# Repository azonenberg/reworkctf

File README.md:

# reworkctf

## What is it?

This is a points-based challenge board intended for practicing of PCB rework and circuit editing skills. This is not a circuit *debug* challenge. The defect for each stage is well documented, your task is to correct it so that the circuit functions properly.

This is also not a learn-to-solder kit. If you're not comfortable populating boards with 0402 passives and larger pitch (0.8mm) BGAs, this is probably not a project you want to undertake until you have the basics down first.

That said, the challenges range from very easy to fairly difficult, so it's totally fine to try some of them then put the board on a shelf for a while until your skills improve. Inner layer circuit edits are among the most challenging rework tasks around, there's a reason they're worth the most points!

This is also intended to be a relatively low-cost board so you can practice without the pressure of reworking a production design with a big FPGA and five-digit price tag. If you destroy a couple of these boards then get the hang of things and your third attempt succeeds, great - you've learned something.

And if the board survives, you've got a STM32H750 dev platform with a UART, two PMODs, a SPI flash, and a lot of LEDs to maybe do something useful with.

IMPORTANT NOTE: Read the challenge list before populating the front side of the PCB. Some of the BGA-site challenges have two versions, an "easy" version which can be done on a bare PCB before populating allowing easy access to the BGA footprint, and a "hard" version which requires you populate the board before doing the rework. Unless you want to do the hard version twice, don't populate the board until you've done the easier ones. This does require doing some of the challenges out of order, unless you want to make two boards and do different challenges on each.

Most notably, the following challenges should be done before populating the BGA:
* Challenge 13

## How do I complete a given challenge?

It's up to you, within reason. If you are able to restore the intended electrical connectivity to the point that the firmware lights up the corresponding "complete" LED and you've followed any restrictions listed in the problem text, you've done it. Please follow the spirit of the challenges, many of them can be "cheated" by jumpering adjacent pins on the MCU together or similar but the point of this board is skill development. If you don't actually fix the intended defect you're not learning.

Almost all challenges are electrically testable by the MCU firmware; those that involve soldermask or silkscreen rework can be graded by visual inspection of the board. If those look good, they probably are.

The [IPC rework guides](https://www.circuitrework.com/guides/guides.html) are a good starting point for general repair techniques.

If you get really stuck on a specific challenge you can message me on Mastodon at[@azonenberg@ioc.exchange](https://ioc.exchange/@azonenberg]) but please make a reasonable attempt to plan a solution first.

## I still have an old rev board, where's the info for that?

The legacy revision 1 challenge, built around a Spartan-3A FPGA, can be found in the "v1" directory and is being kept there in case anybody has an old board and wants to refer to the design. Anyone building the challenge now should use the v2 design which is based on parts that (as of this writing in early 2026) are readily available and inexpensive.

## What tools are required?

A fine point soldering iron, good tweezers, and hot air rework station are a must to attempt any of the challenges. A stereo microscope is strongly recommended.

The silkscreen and solder mask repair challenges require UV or heat cured coating materials and a curing lamp or oven appropriate for the coating chemistry. UV resin allows much more rapid iteration and avoids heat stress on the remainder of the system so we strongly recommend it over heat cure systems.

Surface trace cuts and rerouting require a scalpel or rotary tool/mill with very fine cutters. While the inner layer circuit edits are *possible* to complete with hand scraping or a handheld rotary tool, we strongly recommend use of a 3-axis mill and microscope for the highest grade results and greatest chance of success.

## What are the challenges?

See [the list here](/CHALLENGES.md). Each challenge is marked with silkscreened text on the PCB to make it easy to find.

## What is the "Free Play Area"?

A big pile of component footprints and traces not connected to anything else. Invent your own challenges or use it to practice for the official ones.

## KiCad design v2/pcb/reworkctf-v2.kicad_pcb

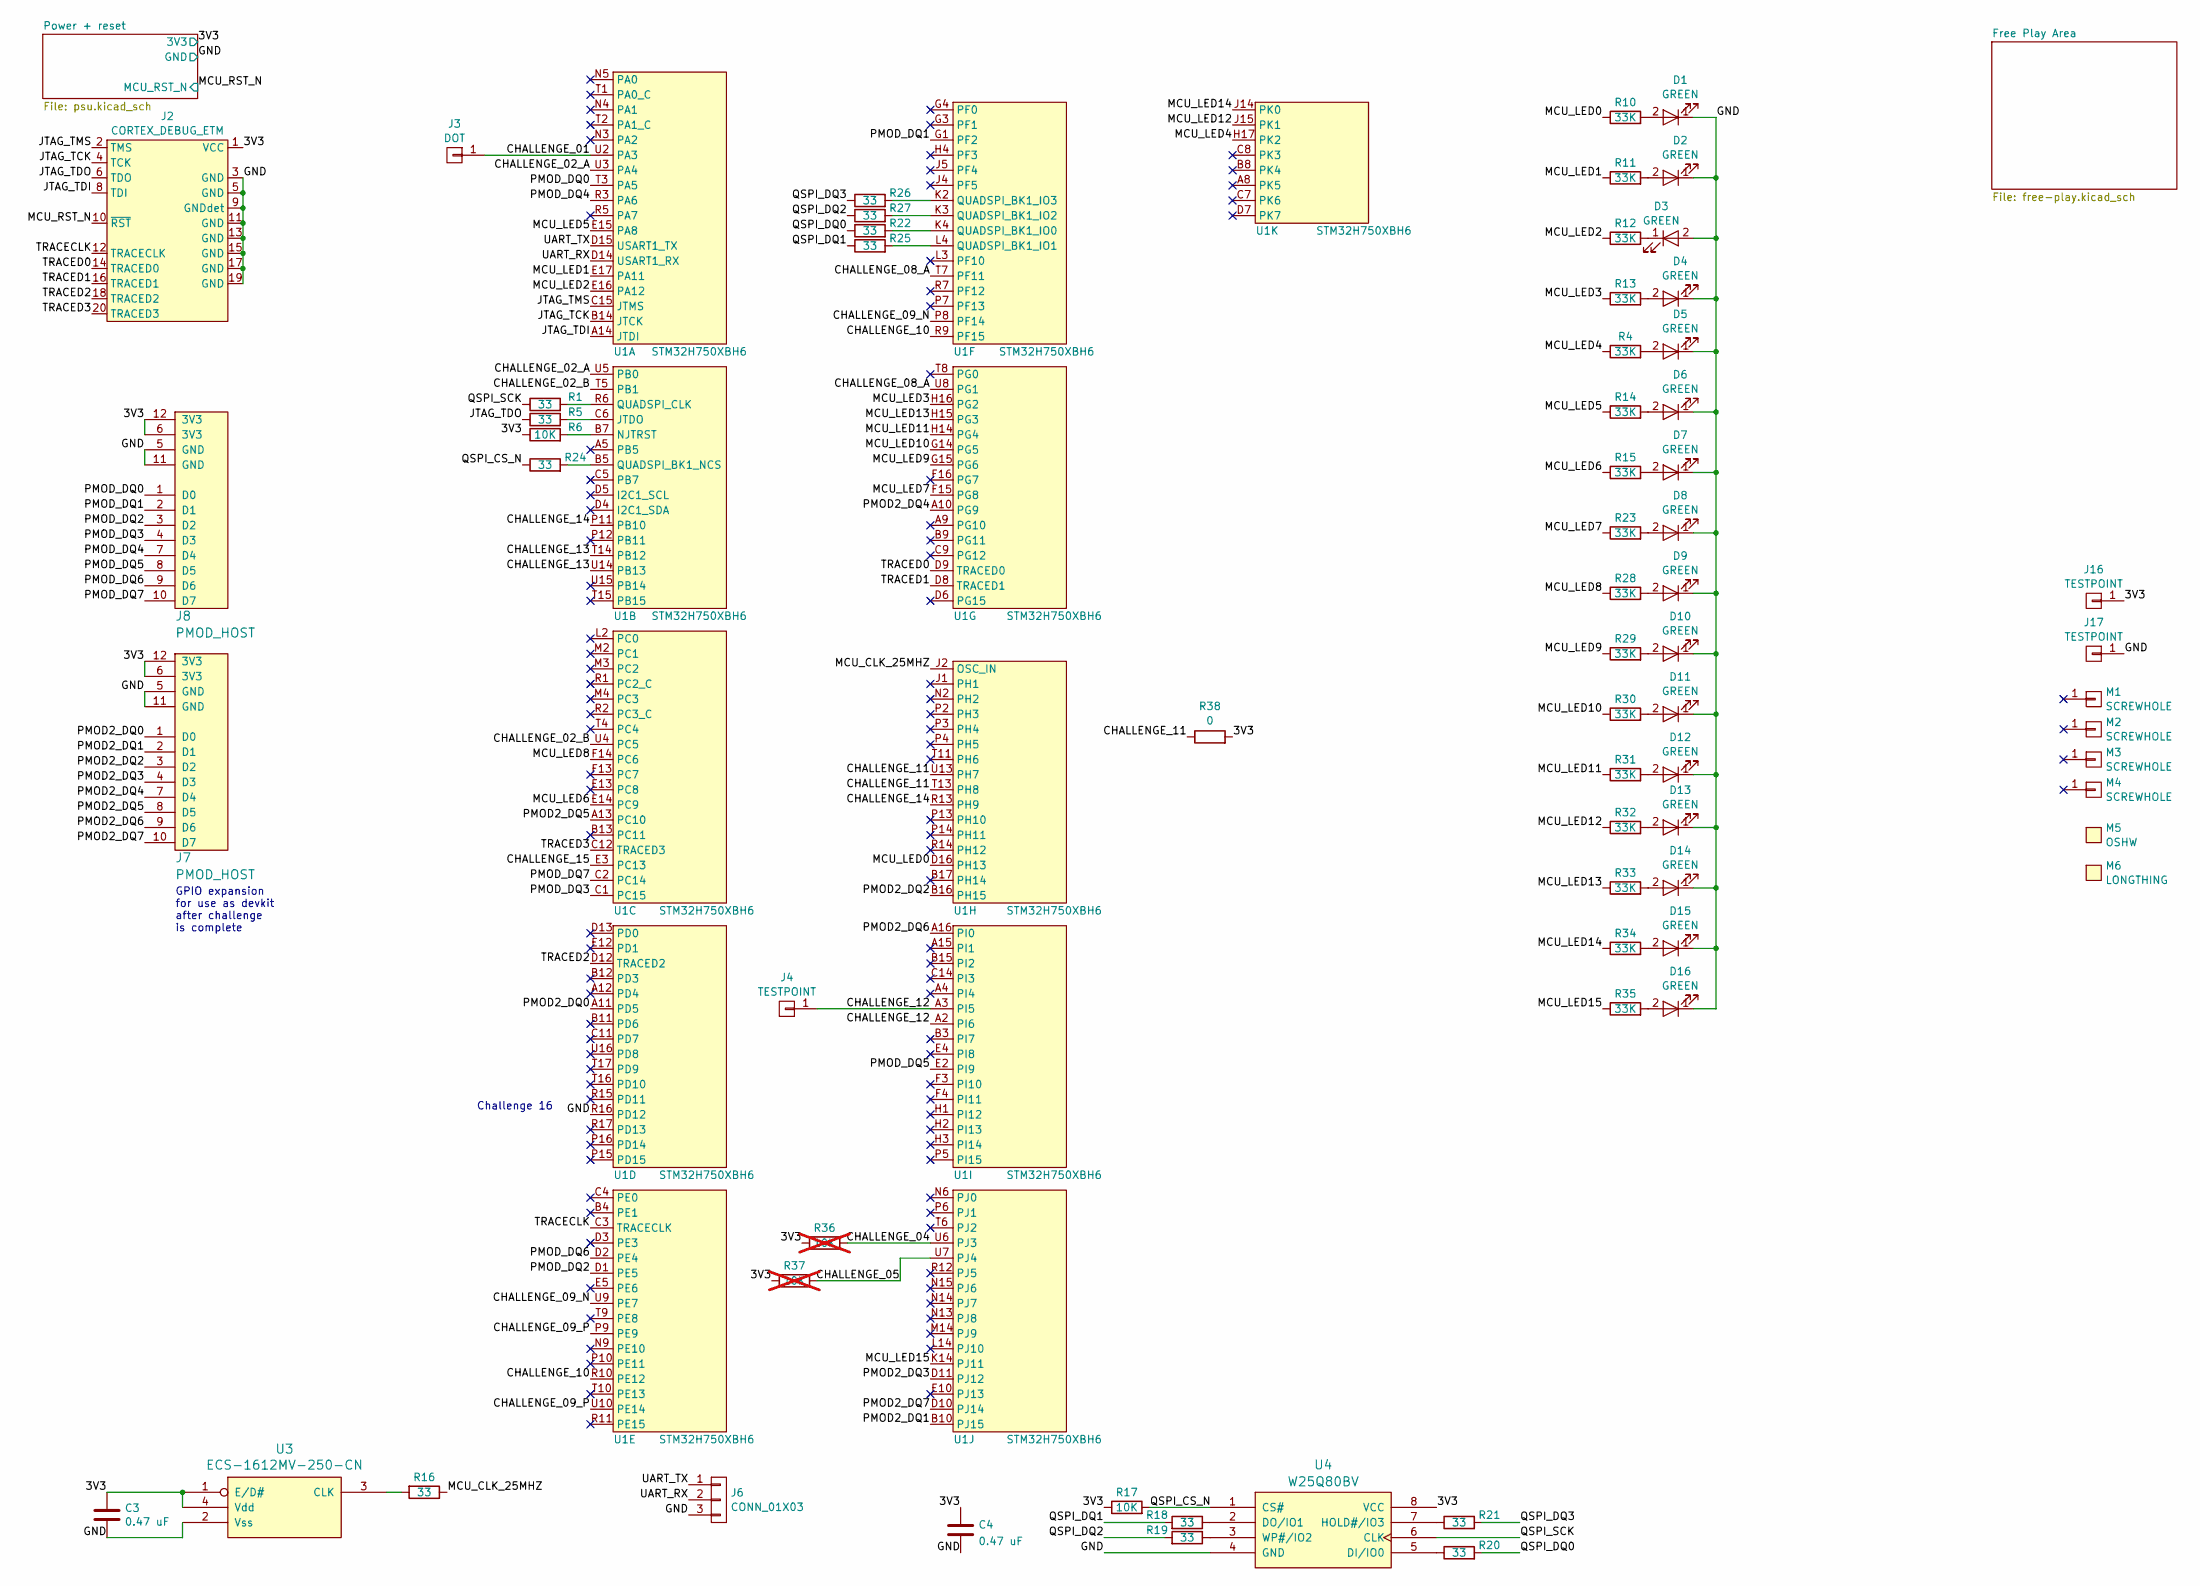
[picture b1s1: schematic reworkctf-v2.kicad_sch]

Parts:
C3, C4: 0.47 uF; EIA_0402_CAP_NOSILK
D1, D2, D3, D4, D5, D6, D7, D8, D9, D10, D11, D12, D13, D14, D15, D16: GREEN; EIA_0402_LED
J2: CORTEX_DEBUG_ETM; CONN_HEADER_1.27MM_2x10_SMT_SAMTEC_FTSH-110-01-L-DV-K
J3: DOT; TESTPOINT_SMT_0.5MM
J4, J16, J17: TESTPOINT; TESTPOINT_SMT_0.5MM
J6: CONN_01X03; CONN_HEADER_2.54MM_1x3_REFLOW
J7, J8: PMOD_HOST; CONN_HEADER_2.54MM_2x6_RA_PMOD_HOST
M1, M2, M3, M4: SCREWHOLE; MECHANICAL_CLEARANCEHOLE_4_40
M5: OSHW; Logo_silk_OSHW_6x6mm
M6: LONGTHING; LONGTHING-1200DPI
R1, R5, R16, R18, R19, R20, R21, R22, R24, R25, R26, R27: 33; EIA_0402_RES_NOSILK
R4, R10, R11, R12, R13, R14, R15, R23, R28, R29, R30, R31, R32, R33, R34, R35: 33K; EIA_0402_RES_NOSILK
R6, R17: 10K; EIA_0402_RES_NOSILK
R36: 10K; EIA_0201_RES_NOSILK; not fitted
R37: 10K; EIA_01005_RES_NOSILK; not fitted
R38: 0; EIA_0402_RES_NOSILK
U1: STM32H750XBH6; BGA_265_14x14_DEPOP_0.8MM
U3: ECS-1612MV-250-CN; OSCILLATOR_1.6x1.2
U4: W25Q80BV; SOIC_8_5.3MM

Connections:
/3V3: C3.1, C4.1, J2.1 (VCC), J7.6 (3V3), J7.12 (3V3), J8.6 (3V3), J8.12 (3V3), J16.1, R6.1, R17.1, R36.1, R37.1, R38.2, U3.1 (E/D#), U3.4 (Vdd), U4.8 (VCC); also elsewhere on the board
/CHALLENGE_01: J3.1, U1.U2 (PA3)
/CHALLENGE_02_A: U1.U3 (PA4), U1.U5 (PB0)
/CHALLENGE_02_B: U1.T5 (PB1), U1.U4 (PC5)
/CHALLENGE_04: R36.2, U1.U6 (PJ3)
/CHALLENGE_05: R37.2, U1.U7 (PJ4)
/CHALLENGE_08_A: U1.T7 (PF11), U1.U8 (PG1)
/CHALLENGE_09_N: U1.P8 (PF14), U1.U9 (PE7)
/CHALLENGE_09_P: U1.P9 (PE9), U1.U10 (PE14)
/CHALLENGE_10: U1.R9 (PF15), U1.R10 (PE12)
/CHALLENGE_11: R38.1, U1.T13 (PH8), U1.U13 (PH7)
/CHALLENGE_12: J4.1, U1.A2 (PI6), U1.A3 (PI5)
/CHALLENGE_13: U1.T14 (PB12), U1.U14 (PB13)
/CHALLENGE_14: U1.P11 (PB10), U1.R13 (PH9)
/CHALLENGE_15: U1.E3 (PC13)
/GND: C3.2, C4.2, D1.1 (K), D2.1 (K), D3.2 (A), D4.1 (K), D5.1 (K), D6.1 (K), D7.1 (K), D8.1 (K), D9.1 (K), D10.1 (K), D11.1 (K), D12.1 (K), D13.1 (K), D14.1 (K), D15.1 (K), D16.1 (K), J2.3 (GND), J2.5 (GND), J2.9 (GNDdet), J2.11 (GND), J2.13 (GND), J2.15 (GND), J2.17 (GND), J2.19 (GND), J6.3, J7.5 (GND), J7.11 (GND), J8.5 (GND), J8.11 (GND), J17.1, U1.R16 (PD12), U3.2 (Vss), U4.4 (GND); also elsewhere on the board
/JTAG_TCK: J2.4 (TCK), U1.B14 (JTCK)
/JTAG_TDI: J2.8 (TDI), U1.A14 (JTDI)
/JTAG_TDO: J2.6 (TDO), R5.1
/JTAG_TMS: J2.2 (TMS), U1.C15 (JTMS)
/MCU_CLK_25MHZ: R16.1, U1.J2 (OSC_IN)
/MCU_LED0: R10.1, U1.D16 (PH13)
/MCU_LED1: R11.1, U1.E17 (PA11)
/MCU_LED2: R12.1, U1.E16 (PA12)
/MCU_LED3: R13.1, U1.H16 (PG2)
/MCU_LED4: R4.1, U1.H17 (PK2)
/MCU_LED5: R14.1, U1.E15 (PA8)
/MCU_LED6: R15.1, U1.E14 (PC9)
/MCU_LED7: R23.1, U1.F15 (PG8)
/MCU_LED8: R28.1, U1.F14 (PC6)
/MCU_LED9: R29.1, U1.G15 (PG6)
/MCU_LED10: R30.1, U1.G14 (PG5)
/MCU_LED11: R31.1, U1.H14 (PG4)
/MCU_LED12: R32.1, U1.J15 (PK1)
/MCU_LED13: R33.1, U1.H15 (PG3)
/MCU_LED14: R34.1, U1.J14 (PK0)
/MCU_LED15: R35.1, U1.K14 (PJ11)
/MCU_RST_N: J2.10 (~RST); also elsewhere on the board
/PMOD2_DQ0: J7.1 (D0), U1.A11 (PD5)
/PMOD2_DQ1: J7.2 (D1), U1.B10 (PJ15)
/PMOD2_DQ2: J7.3 (D2), U1.B16 (PH15)
/PMOD2_DQ3: J7.4 (D3), U1.D11 (PJ12)
/PMOD2_DQ4: J7.7 (D4), U1.A10 (PG9)
/PMOD2_DQ5: J7.8 (D5), U1.A13 (PC10)
/PMOD2_DQ6: J7.9 (D6), U1.A16 (PI0)
/PMOD2_DQ7: J7.10 (D7), U1.D10 (PJ14)
/PMOD_DQ0: J8.1 (D0), U1.T3 (PA5)
/PMOD_DQ1: J8.2 (D1), U1.G1 (PF2)
/PMOD_DQ2: J8.3 (D2), U1.D1 (PE5)
/PMOD_DQ3: J8.4 (D3), U1.C1 (PC15)
/PMOD_DQ4: J8.7 (D4), U1.R3 (PA6)
/PMOD_DQ5: J8.8 (D5), U1.E2 (PI9)
/PMOD_DQ6: J8.9 (D6), U1.D2 (PE4)
/PMOD_DQ7: J8.10 (D7), U1.C2 (PC14)
/QSPI_CS_N: R17.2, R24.1, U4.1 (CS#)
/QSPI_DQ0: R20.2, R22.1
/QSPI_DQ1: R18.2, R25.1
/QSPI_DQ2: R19.2, R27.1
/QSPI_DQ3: R21.2, R26.1
/QSPI_SCK: R1.1, U4.6 (CLK)
/TRACECLK: J2.12 (TRACECLK), U1.C3 (TRACECLK)
/TRACED0: J2.14 (TRACED0), U1.D9 (TRACED0)
/TRACED1: J2.16 (TRACED1), U1.D8 (TRACED1)
/TRACED2: J2.18 (TRACED2), U1.D12 (TRACED2)
/TRACED3: J2.20 (TRACED3), U1.C12 (TRACED3)
/UART_RX: J6.2, U1.D14 (USART1_RX)
/UART_TX: J6.1, U1.D15 (USART1_TX)
unnamed: D1.2 (A), R10.2
unnamed: D2.2 (A), R11.2
unnamed: D3.1 (K), R12.2
unnamed: D4.2 (A), R13.2
unnamed: D5.2 (A), R4.2
unnamed: D6.2 (A), R14.2
unnamed: D7.2 (A), R15.2
unnamed: D8.2 (A), R23.2
unnamed: D9.2 (A), R28.2
unnamed: D10.2 (A), R29.2
unnamed: D11.2 (A), R30.2
unnamed: D12.2 (A), R31.2
unnamed: D13.2 (A), R32.2
unnamed: D14.2 (A), R33.2
unnamed: D15.2 (A), R34.2
unnamed: D16.2 (A), R35.2
unnamed: R1.2, U1.R6 (QUADSPI_CLK)
unnamed: R5.2, U1.C6 (JTDO)
unnamed: R6.2, U1.B7 (NJTRST)
unnamed: R24.2, U1.B5 (QUADSPI_BK1_NCS)
unnamed: R26.2, U1.K2 (QUADSPI_BK1_IO3)
unnamed: R27.2, U1.K3 (QUADSPI_BK1_IO2)
unnamed: R22.2, U1.K4 (QUADSPI_BK1_IO0)
unnamed: R25.2, U1.L4 (QUADSPI_BK1_IO1)
unnamed: R16.2, U3.3 (CLK)
unnamed: R20.1, U4.5 (DI/IO0)
unnamed: R18.1, U4.2 (DO/IO1)
unnamed: R21.1, U4.7 (HOLD#/IO3)
unnamed: R19.1, U4.3 (WP#/IO2)

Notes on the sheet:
Challenge 16
GPIO expansion for use as devkit after challenge is complete

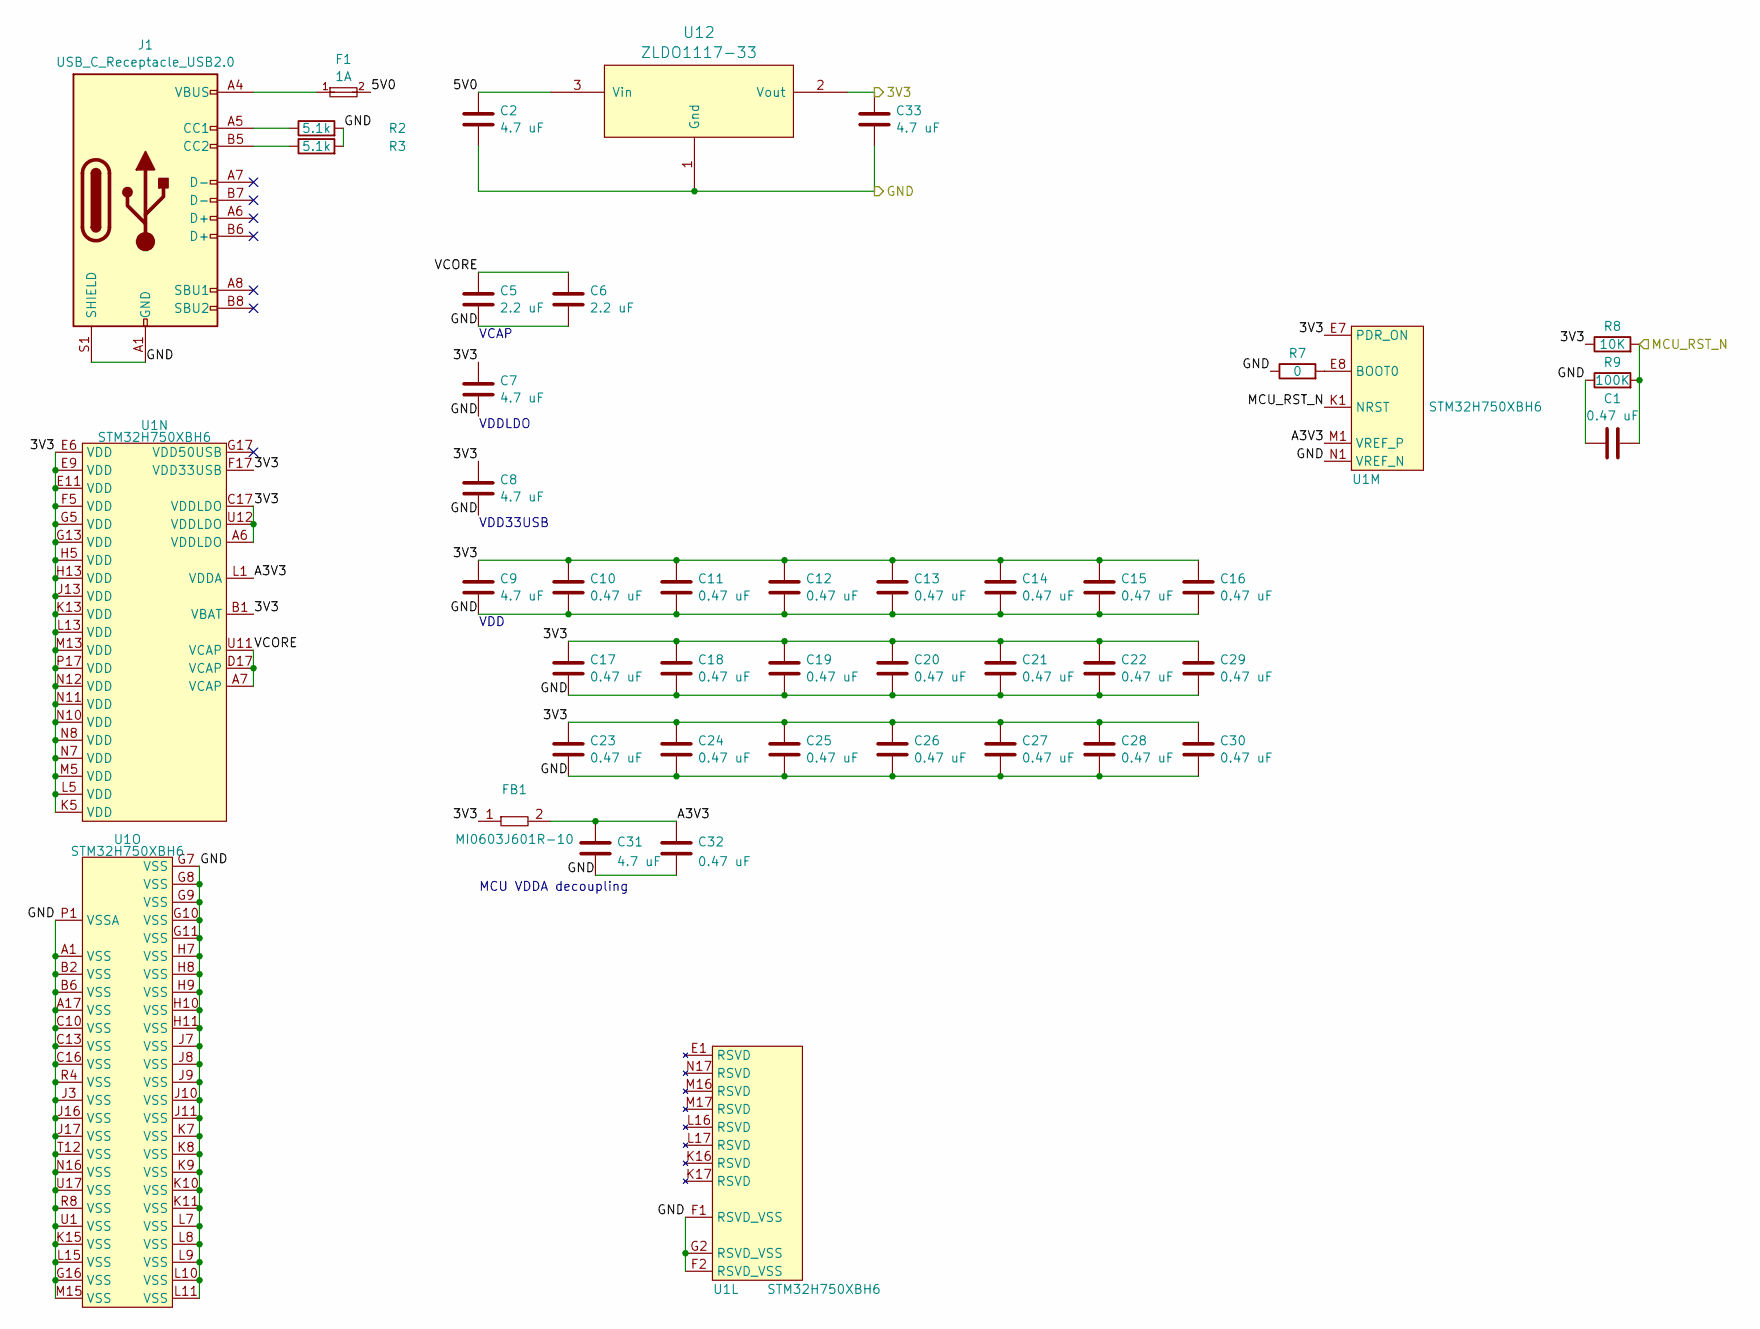
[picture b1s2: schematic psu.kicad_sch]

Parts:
C1, C10, C11, C12, C13, C14, C15, C16, C17, C18, C19, C20, C21, C22, C23, C24, C25, C26, C27, C28, C29, C30, C32: 0.47 uF; EIA_0402_CAP_NOSILK
C2, C7, C8, C9, C31, C33: 4.7 uF; EIA_0603_CAP_NOSILK
C5, C6: 2.2 uF; EIA_0603_CAP_NOSILK
F1: 1A; EIA_0402_RES_NOSILK
FB1: MI0603J601R-10; EIA_0603_INDUCTOR_NOSILK
J1: USB_C_Receptacle_USB2.0; GCT_USB4500-03-0-A
R2, R3: 5.1k; EIA_0402_RES_NOSILK
R7: 0; EIA_0402_RES_NOSILK
R8: 10K; EIA_0402_RES_NOSILK
R9: 100K; EIA_0402_RES_NOSILK
U1: STM32H750XBH6; BGA_265_14x14_DEPOP_0.8MM
U12: ZLDO1117-33; SOT223-4

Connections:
/3V3: C7.1, C8.1, C9.1, C10.1, C11.1, C12.1, C13.1, C14.1, C15.1, C16.1, C17.1, C18.1, C19.1, C20.1, C21.1, C22.1, C23.1, C24.1, C25.1, C26.1, C27.1, C28.1, C29.1, C30.1, C33.1, FB1.1, R8.1, U1.A6 (VDDLDO), U1.B1 (VBAT), U1.C17 (VDDLDO), U1.E6 (VDD), U1.E7 (PDR_ON), U1.E9 (VDD), U1.E11 (VDD), U1.F5 (VDD), U1.F17 (VDD33USB), U1.G5 (VDD), U1.G13 (VDD), U1.H5 (VDD), U1.H13 (VDD), U1.J13 (VDD), U1.K5 (VDD), U1.K13 (VDD), U1.L5 (VDD), U1.L13 (VDD), U1.M5 (VDD), U1.M13 (VDD), U1.N7 (VDD), U1.N8 (VDD), U1.N10 (VDD), U1.N11 (VDD), U1.N12 (VDD), U1.P17 (VDD), U1.U12 (VDDLDO), U12.2 (Vout); also elsewhere on the board
/GND: C1.1, C2.2, C5.2, C6.2, C7.2, C8.2, C9.2, C10.2, C11.2, C12.2, C13.2, C14.2, C15.2, C16.2, C17.2, C18.2, C19.2, C20.2, C21.2, C22.2, C23.2, C24.2, C25.2, C26.2, C27.2, C28.2, C29.2, C30.2, C31.2, C32.2, C33.2, J1.A1 (GND), J1.A12 (GND), J1.B1 (GND), J1.B12 (GND), J1.S1 (SHIELD), R2.2, R3.2, R7.1, R9.1, U1.A1 (VSS), U1.A17 (VSS), U1.B2 (VSS), U1.B6 (VSS), U1.C10 (VSS), U1.C13 (VSS), U1.C16 (VSS), U1.F1 (RSVD_VSS), U1.F2 (RSVD_VSS), U1.G2 (RSVD_VSS), U1.G7 (VSS), U1.G8 (VSS), U1.G9 (VSS), U1.G10 (VSS), U1.G11 (VSS), U1.G16 (VSS), U1.H7 (VSS), U1.H8 (VSS), U1.H9 (VSS), U1.H10 (VSS), U1.H11 (VSS), U1.J3 (VSS), U1.J7 (VSS), U1.J8 (VSS), U1.J9 (VSS), U1.J10 (VSS), U1.J11 (VSS), U1.J16 (VSS), U1.J17 (VSS), U1.K7 (VSS), U1.K8 (VSS), U1.K9 (VSS), U1.K10 (VSS), U1.K11 (VSS), U1.K15 (VSS), U1.L7 (VSS), U1.L8 (VSS), U1.L9 (VSS), U1.L10 (VSS), U1.L11 (VSS), U1.L15 (VSS), U1.M15 (VSS), U1.N1 (VREF_N), U1.N16 (VSS), U1.P1 (VSSA), U1.R4 (VSS), U1.R8 (VSS), U1.T12 (VSS), U1.U1 (VSS), U1.U17 (VSS), U12.1 (Gnd); also elsewhere on the board
/MCU_RST_N: C1.2, R8.2, R9.2, U1.K1 (NRST); also elsewhere on the board
/Power + reset/5V0: C2.1, F1.2, U12.3 (Vin)
/Power + reset/A3V3: C31.1, C32.1, FB1.2, U1.L1 (VDDA), U1.M1 (VREF_P)
/Power + reset/VCORE: C5.1, C6.1, U1.A7 (VCAP), U1.D17 (VCAP), U1.U11 (VCAP)
unnamed: F1.1, J1.A4 (VBUS), J1.A9 (VBUS), J1.B4 (VBUS), J1.B9 (VBUS)
unnamed: J1.A5 (CC1), R2.1
unnamed: J1.B5 (CC2), R3.1
unnamed: R7.2, U1.E8 (BOOT0)

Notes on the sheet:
VDD
MCU VDDA decoupling
VDDLDO
VCAP
VDD33USB

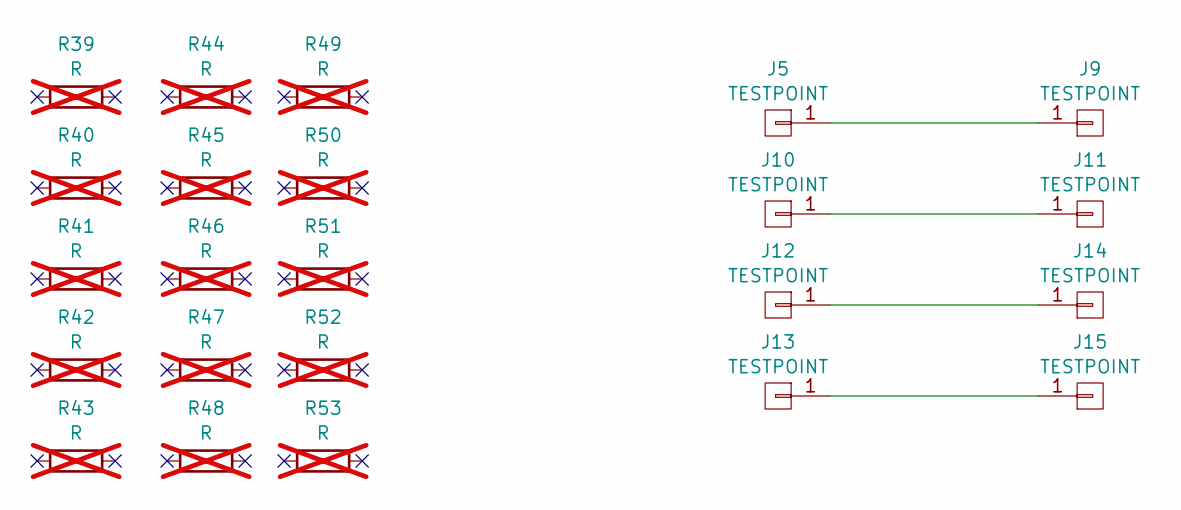
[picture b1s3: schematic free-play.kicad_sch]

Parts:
J5, J9, J10, J11, J12, J13, J14, J15: TESTPOINT; TESTPOINT_SMT_0.5MM
R39, R40, R41, R42, R43, R44, R45, R46, R47, R48, R49, R50, R51, R52, R53: R; EIA_0402_RES_NOSILK; not fitted

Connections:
unnamed: J5.1, J9.1
unnamed: J10.1, J11.1
unnamed: J12.1, J14.1
unnamed: J13.1, J15.1

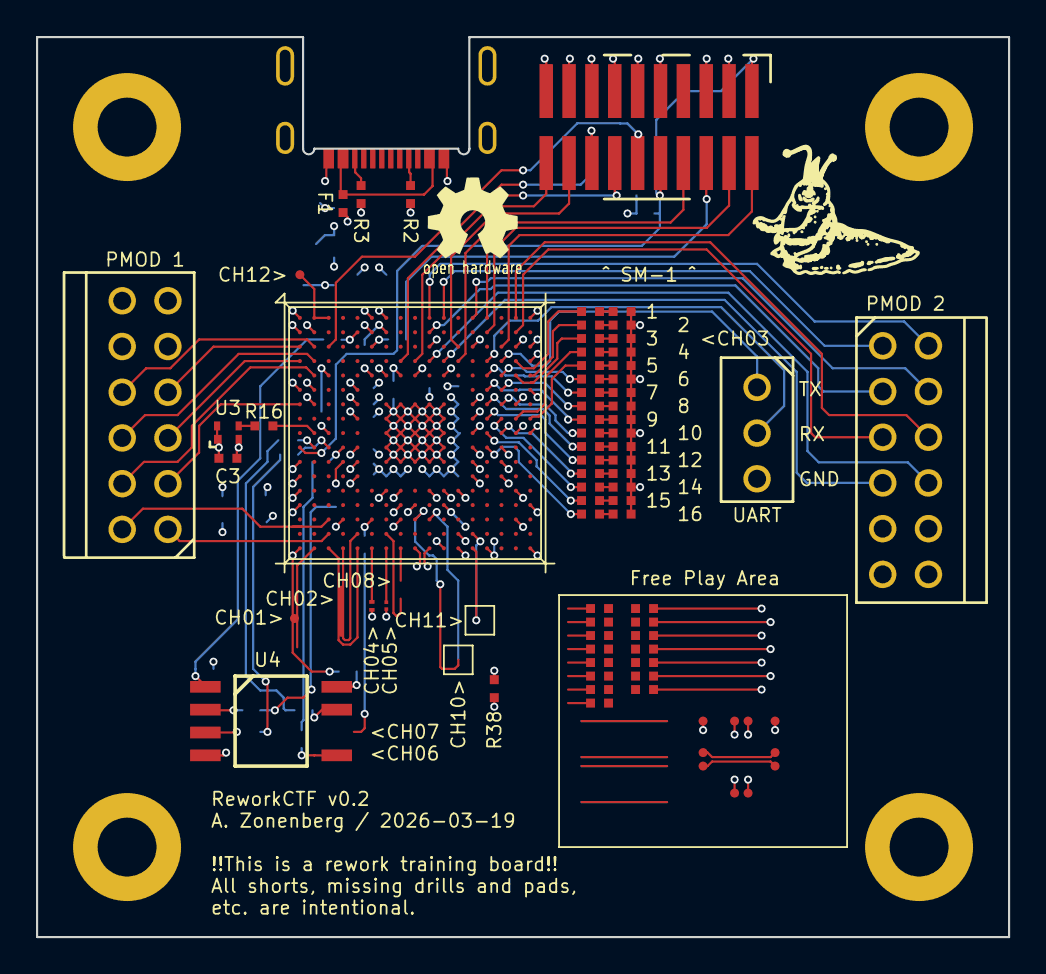
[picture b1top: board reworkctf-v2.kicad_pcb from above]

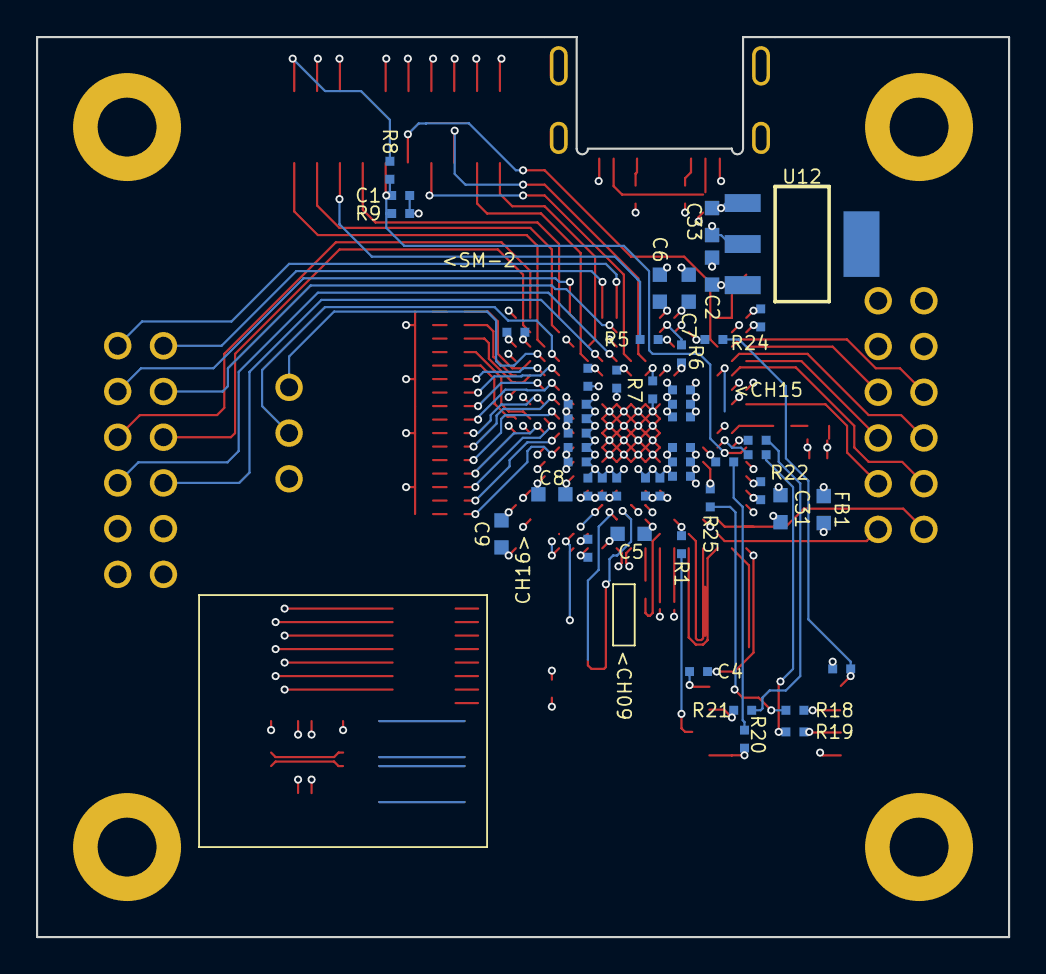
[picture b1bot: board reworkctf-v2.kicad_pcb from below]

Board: 4 copper layers, 54.0 x 50.0 mm, 131 parts (50 on the bottom side), 105 nets.

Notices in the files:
firmware/bsp/hwinit.cpp:
Copyright (c) 2023-2026 Andrew D. Zonenberg and contributors
All rights reserved.
